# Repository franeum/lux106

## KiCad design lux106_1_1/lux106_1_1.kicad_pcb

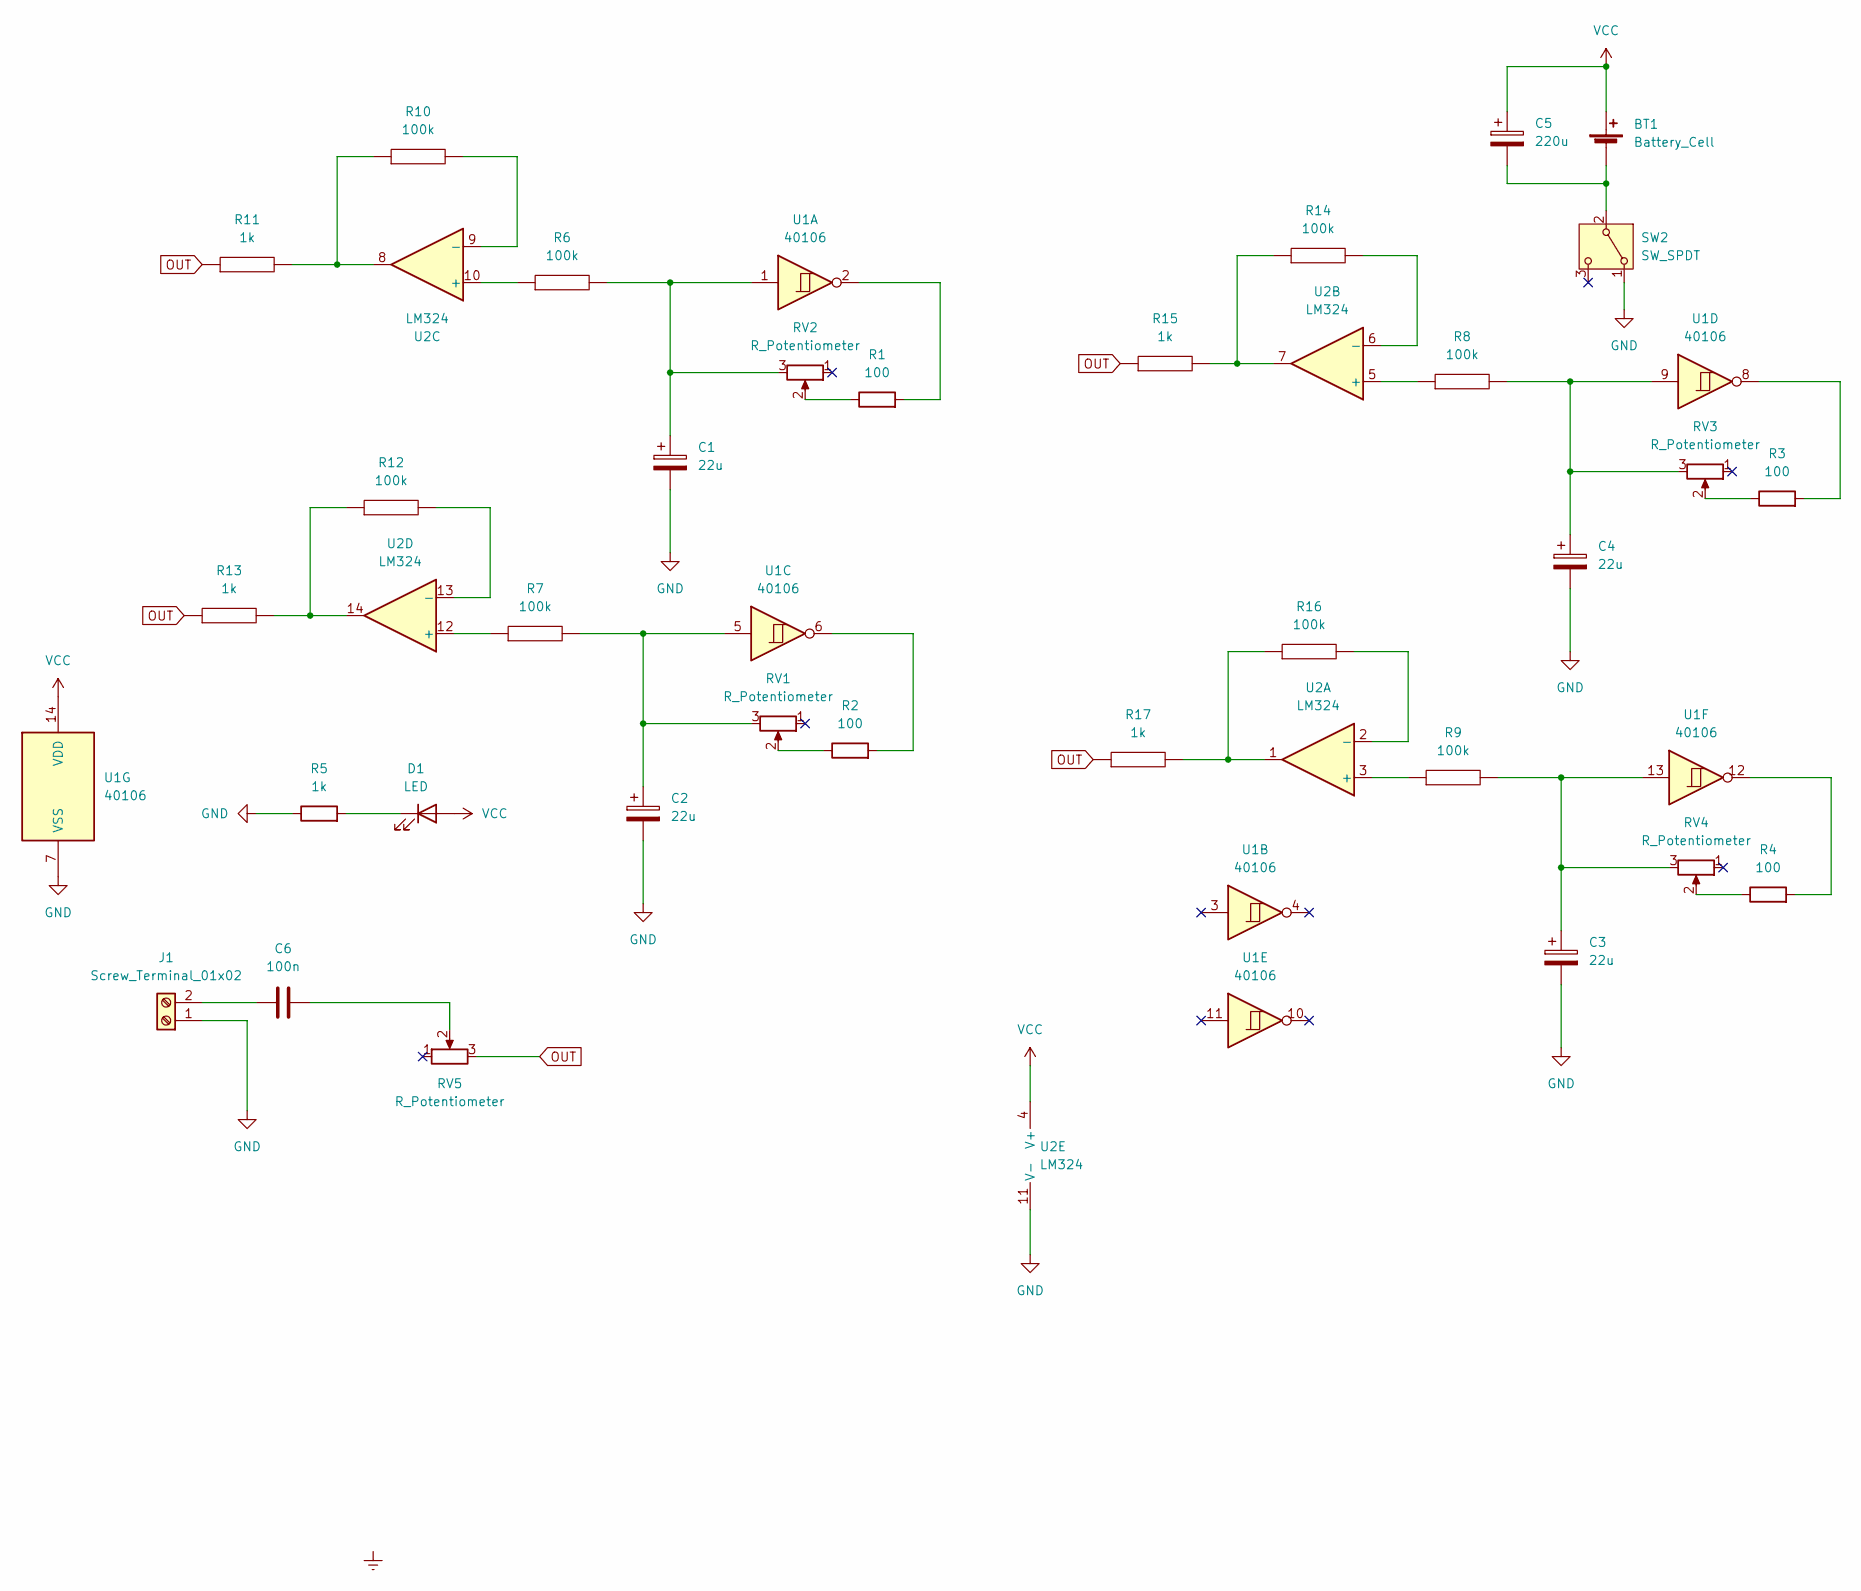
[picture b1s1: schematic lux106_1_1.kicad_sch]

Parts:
BT1: Battery_Cell; BatteryHolder_MPD_BA9VPC_1xPP3
C1, C2, C3, C4: 22u; CP_Radial_D5.0mm_P2.50mm
C5: 220u; CP_Radial_D6.3mm_P2.50mm
C6: 100n; C_Disc_D3.4mm_W2.1mm_P2.50mm
D1: LED; LED_D5.0mm_Clear
J1: Screw_Terminal_01x02; TerminalBlock_bornier-2_P5.08mm
R1, R2, R3, R4: 100; R_Axial_DIN0207_L6.3mm_D2.5mm_P7.62mm_Horizontal
R5, R11, R13, R15, R17: 1k; R_Axial_DIN0207_L6.3mm_D2.5mm_P7.62mm_Horizontal
R6, R7, R8, R9, R10, R12, R14, R16: 100k; R_Axial_DIN0207_L6.3mm_D2.5mm_P7.62mm_Horizontal
RV1, RV2, RV3, RV4, RV5: R_Potentiometer; Potentiometer_Alps_RK097_Single_Horizontal
SW2: SW_SPDT; mini_SPDT_switch
U1: 40106; DIP-14_W7.62mm_Socket
U2: LM324; DIP-14_W7.62mm_Socket

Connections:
GND: C1.2, C2.2, C3.2, C4.2, J1.1, R5.1, SW2.1 (A), U1.7 (VSS), U2.11 (V-)
unnamed: BT1.2 (-), C5.2, SW2.2 (B)
unnamed: C1.1, R6.2, RV2.3, U1.1
unnamed: C2.1, R7.2, RV1.3, U1.5
unnamed: C3.1, R9.2, RV4.3, U1.13
unnamed: C4.1, R8.2, RV3.3, U1.9
unnamed: C6.2, RV5.2
unnamed: D1.1 (K), R5.2
unnamed: C6.1, J1.2
unnamed: R1.1, RV2.2
unnamed: R1.2, U1.2
unnamed: R2.1, RV1.2
unnamed: R2.2, U1.6
unnamed: R3.1, RV3.2
unnamed: R3.2, U1.8
unnamed: R4.1, RV4.2
unnamed: R4.2, U1.12
unnamed: R10.1, R11.2, U2.8
unnamed: R12.1, R13.2, U2.14
unnamed: R14.1, R15.2, U2.7
unnamed: R16.1, R17.2, U2.1
unnamed: R9.1, U2.3 (+)
unnamed: R16.2, U2.2 (-)
unnamed: R8.1, U2.5 (+)
unnamed: R14.2, U2.6 (-)
unnamed: R6.1, U2.10 (+)
unnamed: R10.2, U2.9 (-)
unnamed: R7.1, U2.12 (+)
unnamed: R12.2, U2.13 (-)
OUT: R11.1, R13.1, R15.1, R17.1, RV5.3
VCC: BT1.1 (+), C5.1, D1.2 (A), U1.14 (VDD), U2.4 (V+)

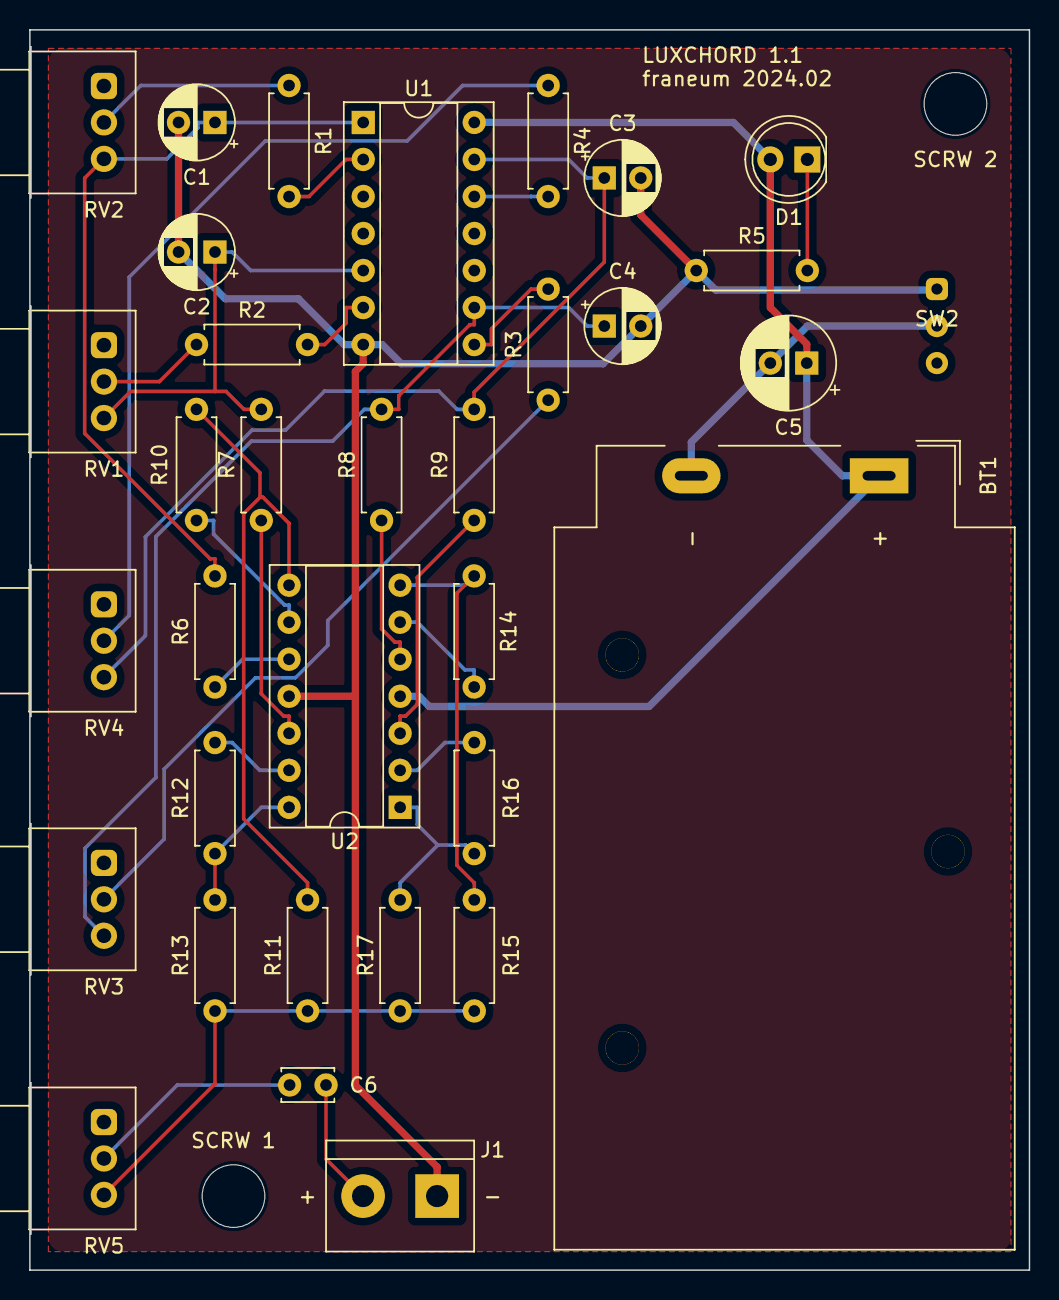
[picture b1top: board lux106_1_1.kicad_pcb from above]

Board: 2 copper layers, 68.6 x 85.1 mm, 36 parts (0 on the bottom side), 31 nets.

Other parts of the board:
SCRW 1, SCRW 2: MountingHole_4.3mm_M4

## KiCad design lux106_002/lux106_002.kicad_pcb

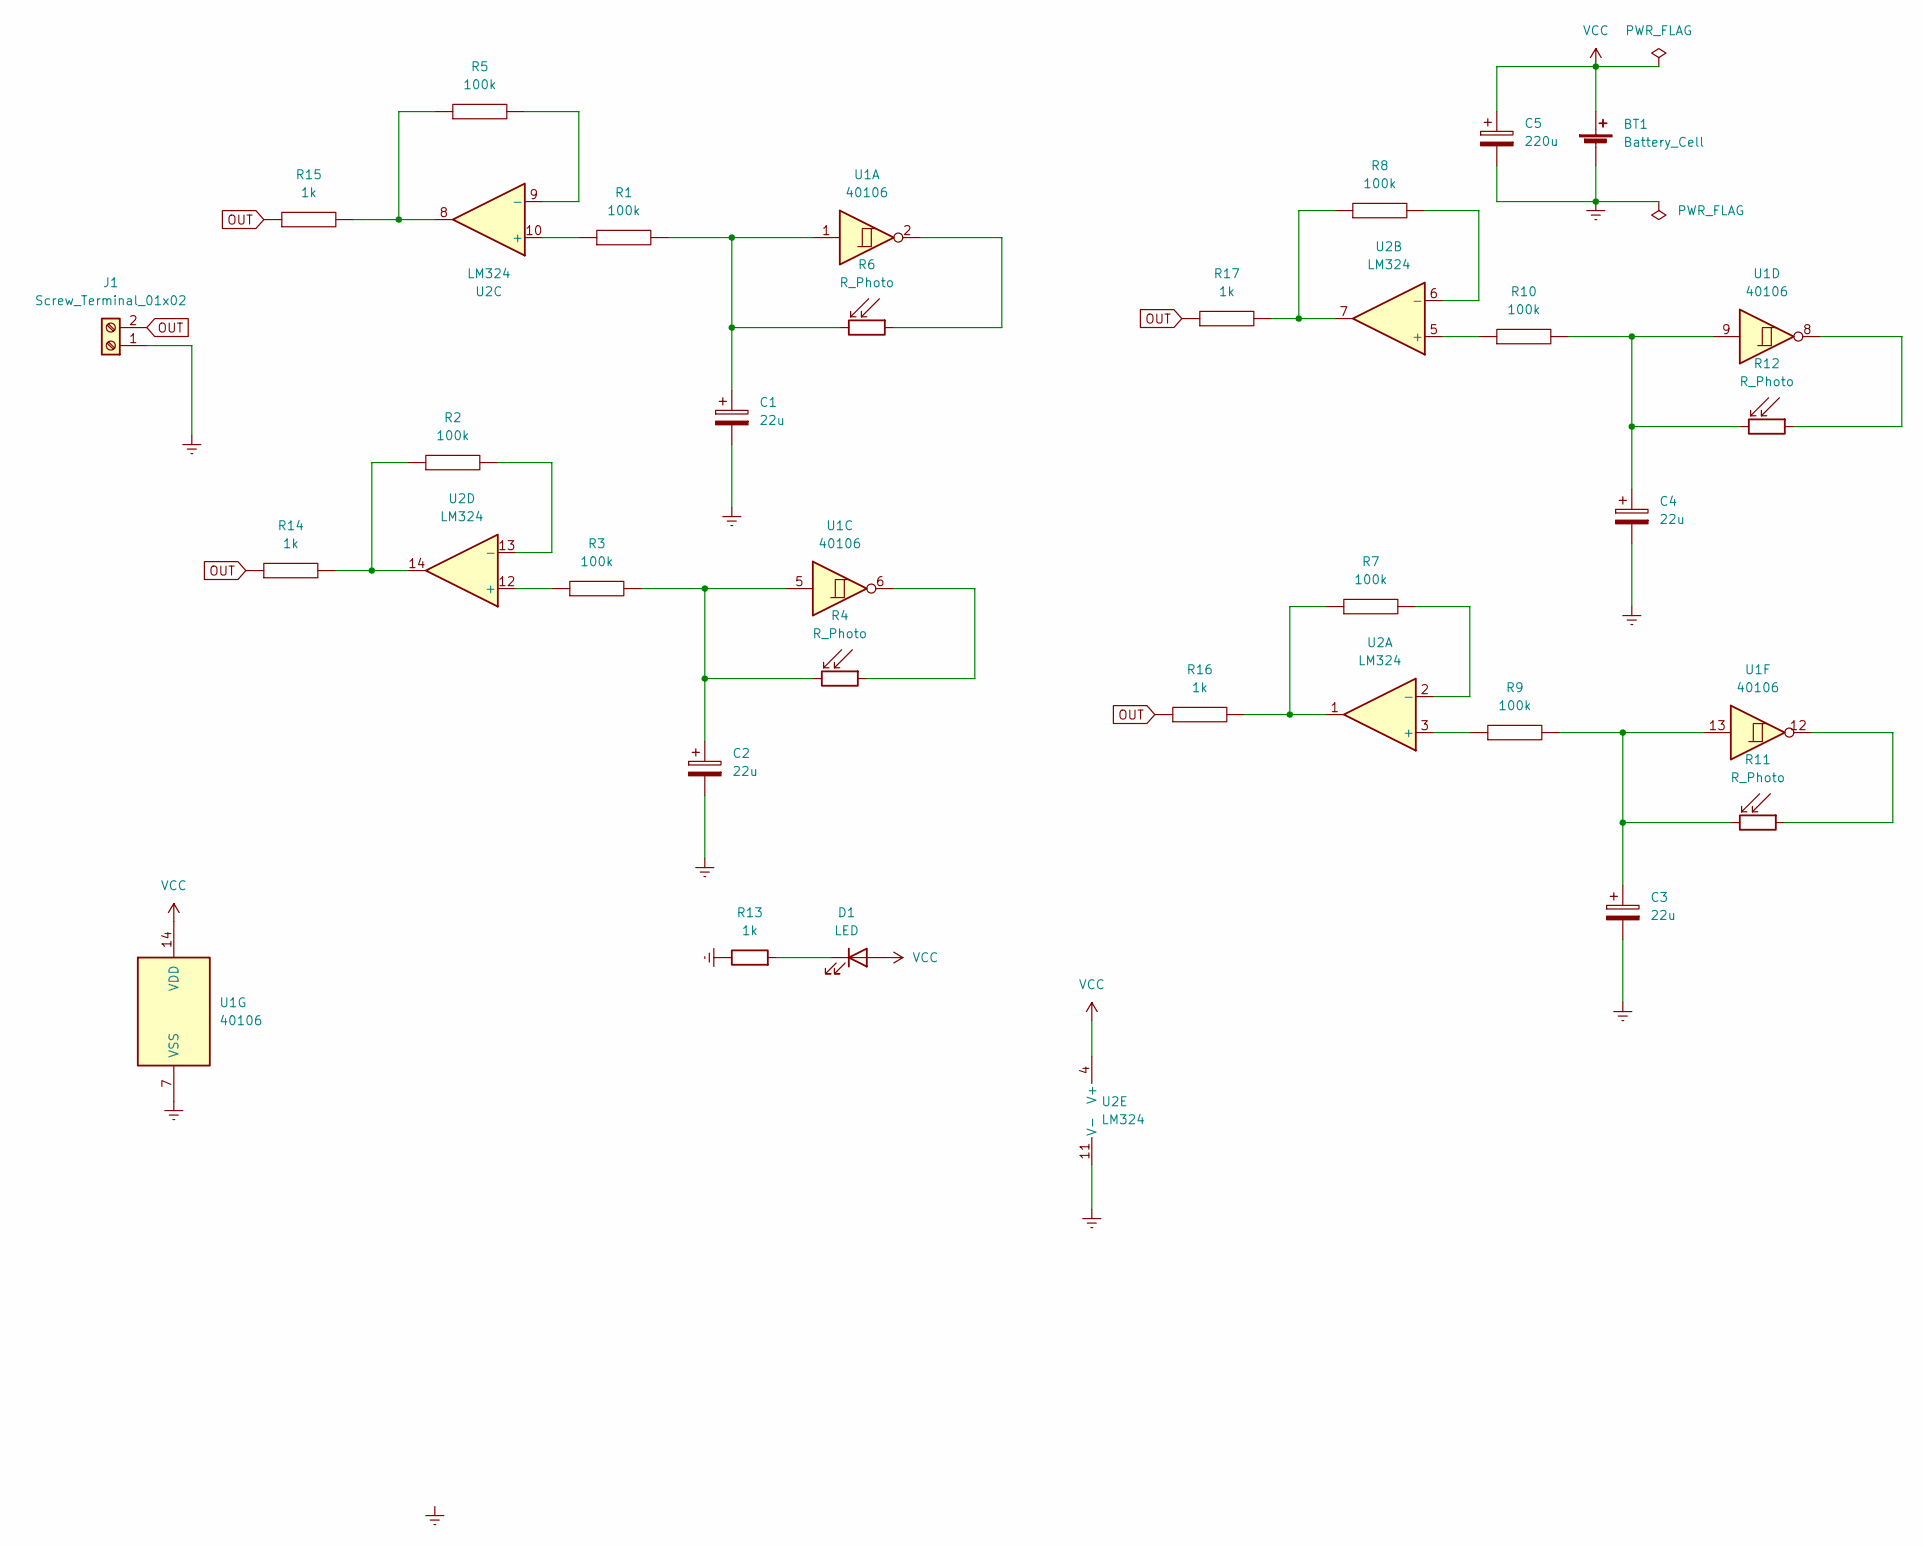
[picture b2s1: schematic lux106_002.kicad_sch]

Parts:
BT1: Battery_Cell; TerminalBlock_Altech_AK300-2_P5.00mm
C1, C2, C3, C4: 22u; CP_Radial_D5.0mm_P2.50mm
C5: 220u; CP_Radial_D6.3mm_P2.50mm
D1: LED; LED_D5.0mm_Clear
J1: Screw_Terminal_01x02; TerminalBlock_Altech_AK300-2_P5.00mm
R1, R2, R3, R5, R7, R8, R9, R10: 100k; R_Axial_DIN0309_L9.0mm_D3.2mm_P2.54mm_Vertical
R4, R6, R11, R12: R_Photo; R_Axial_DIN0204_L3.6mm_D1.6mm_P2.54mm_Vertical
R13, R14, R15, R16, R17: 1k; R_Axial_DIN0309_L9.0mm_D3.2mm_P2.54mm_Vertical
U1: 40106; DIP-14_W7.62mm_Socket
U2: LM324; DIP-14_W7.62mm_Socket

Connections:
Earth: BT1.2 (-), C1.2, C2.2, C3.2, C4.2, C5.2, J1.1, R13.1, U1.7 (VSS), U2.11 (V-)
unnamed: C1.1, R1.2, R6.2, U1.1
unnamed: C2.1, R3.2, R4.2, U1.5
unnamed: C3.1, R9.2, R11.2, U1.13
unnamed: C4.1, R10.2, R12.2, U1.9
unnamed: D1.1 (K), R13.2
unnamed: R1.1, U2.10 (+)
unnamed: R2.2, U2.13 (-)
unnamed: R3.1, U2.12 (+)
unnamed: R4.1, U1.6
unnamed: R5.2, U2.9 (-)
unnamed: R6.1, U1.2
unnamed: R7.2, U2.2 (-)
unnamed: R8.2, U2.6 (-)
unnamed: R9.1, U2.3 (+)
unnamed: R10.1, U2.5 (+)
unnamed: R11.1, U1.12
unnamed: R12.1, U1.8
unnamed: R2.1, R14.2, U2.14
unnamed: R5.1, R15.2, U2.8
unnamed: R7.1, R16.2, U2.1
unnamed: R8.1, R17.2, U2.7
OUT: J1.2, R14.1, R15.1, R16.1, R17.1
VCC: BT1.1 (+), C5.1, D1.2 (A), U1.14 (VDD), U2.4 (V+)

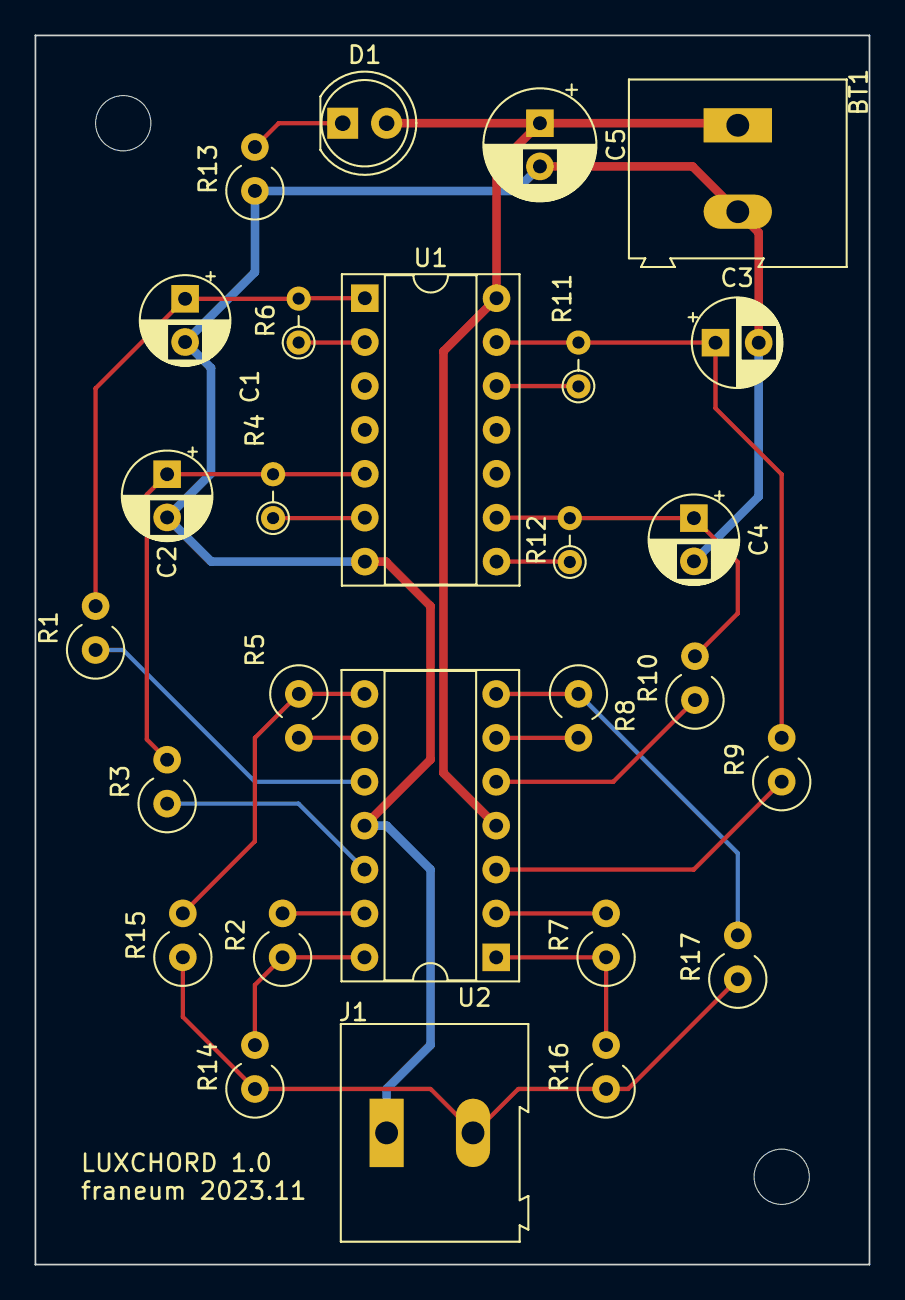
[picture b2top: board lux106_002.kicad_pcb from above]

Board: 2 copper layers, 48.3 x 71.1 mm, 27 parts (0 on the bottom side), 24 nets.

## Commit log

2023-11-19 new sbroglia
2023-11-19 fix version 1.0
2023-12-01 deleted old
2024-02-01 v.1.1
2024-02-02 update gerber & drill files
2024-02-02 update zip gerber
